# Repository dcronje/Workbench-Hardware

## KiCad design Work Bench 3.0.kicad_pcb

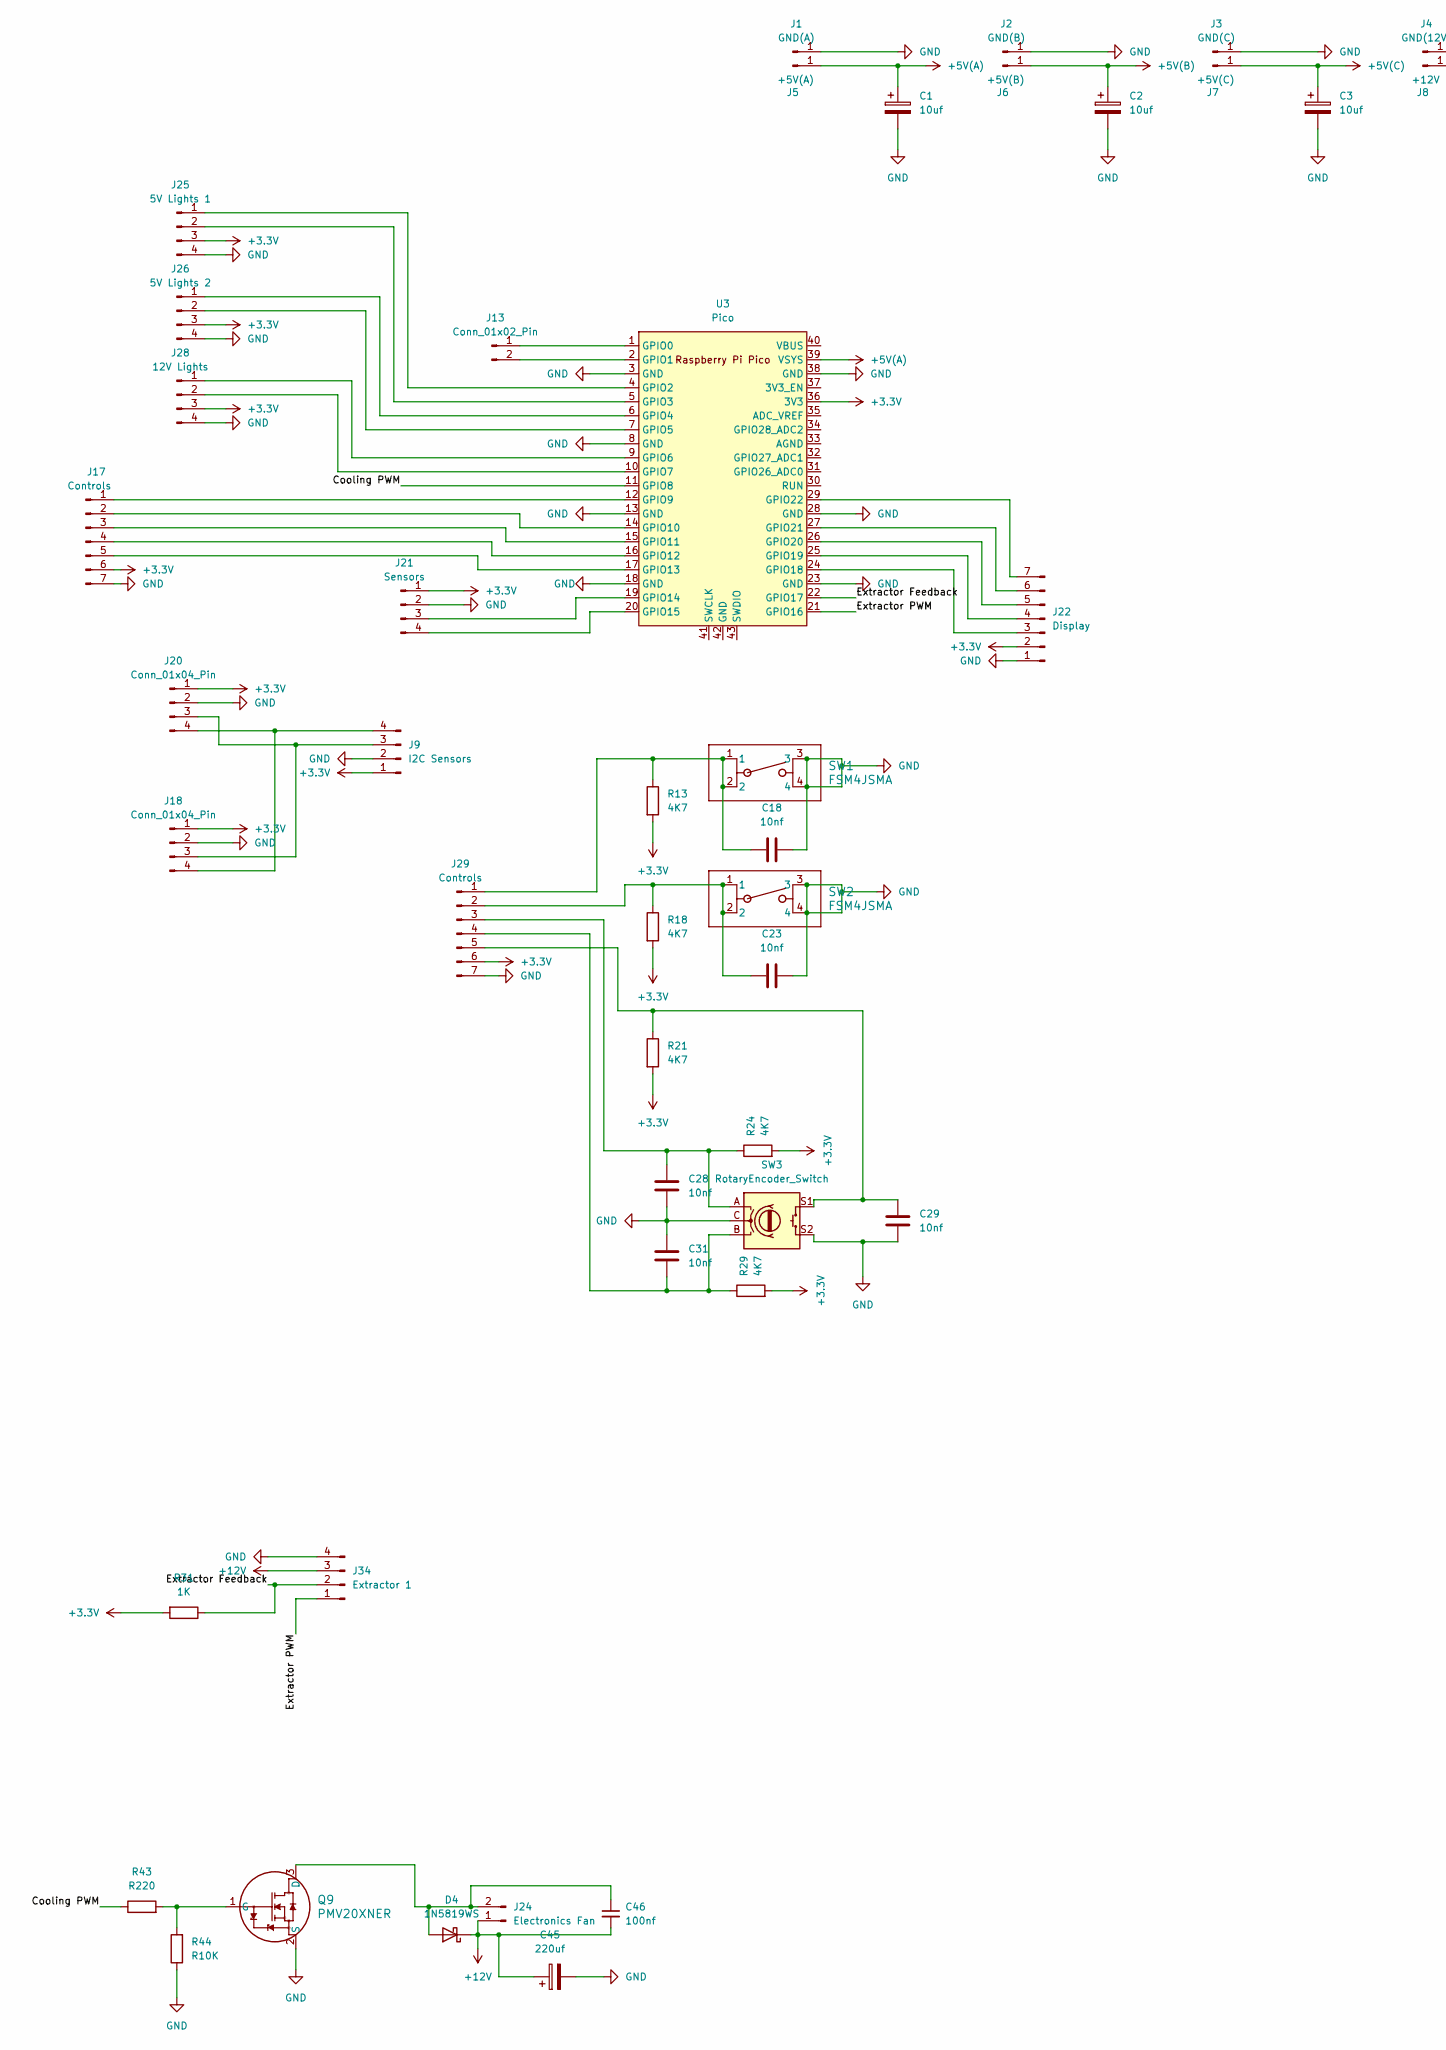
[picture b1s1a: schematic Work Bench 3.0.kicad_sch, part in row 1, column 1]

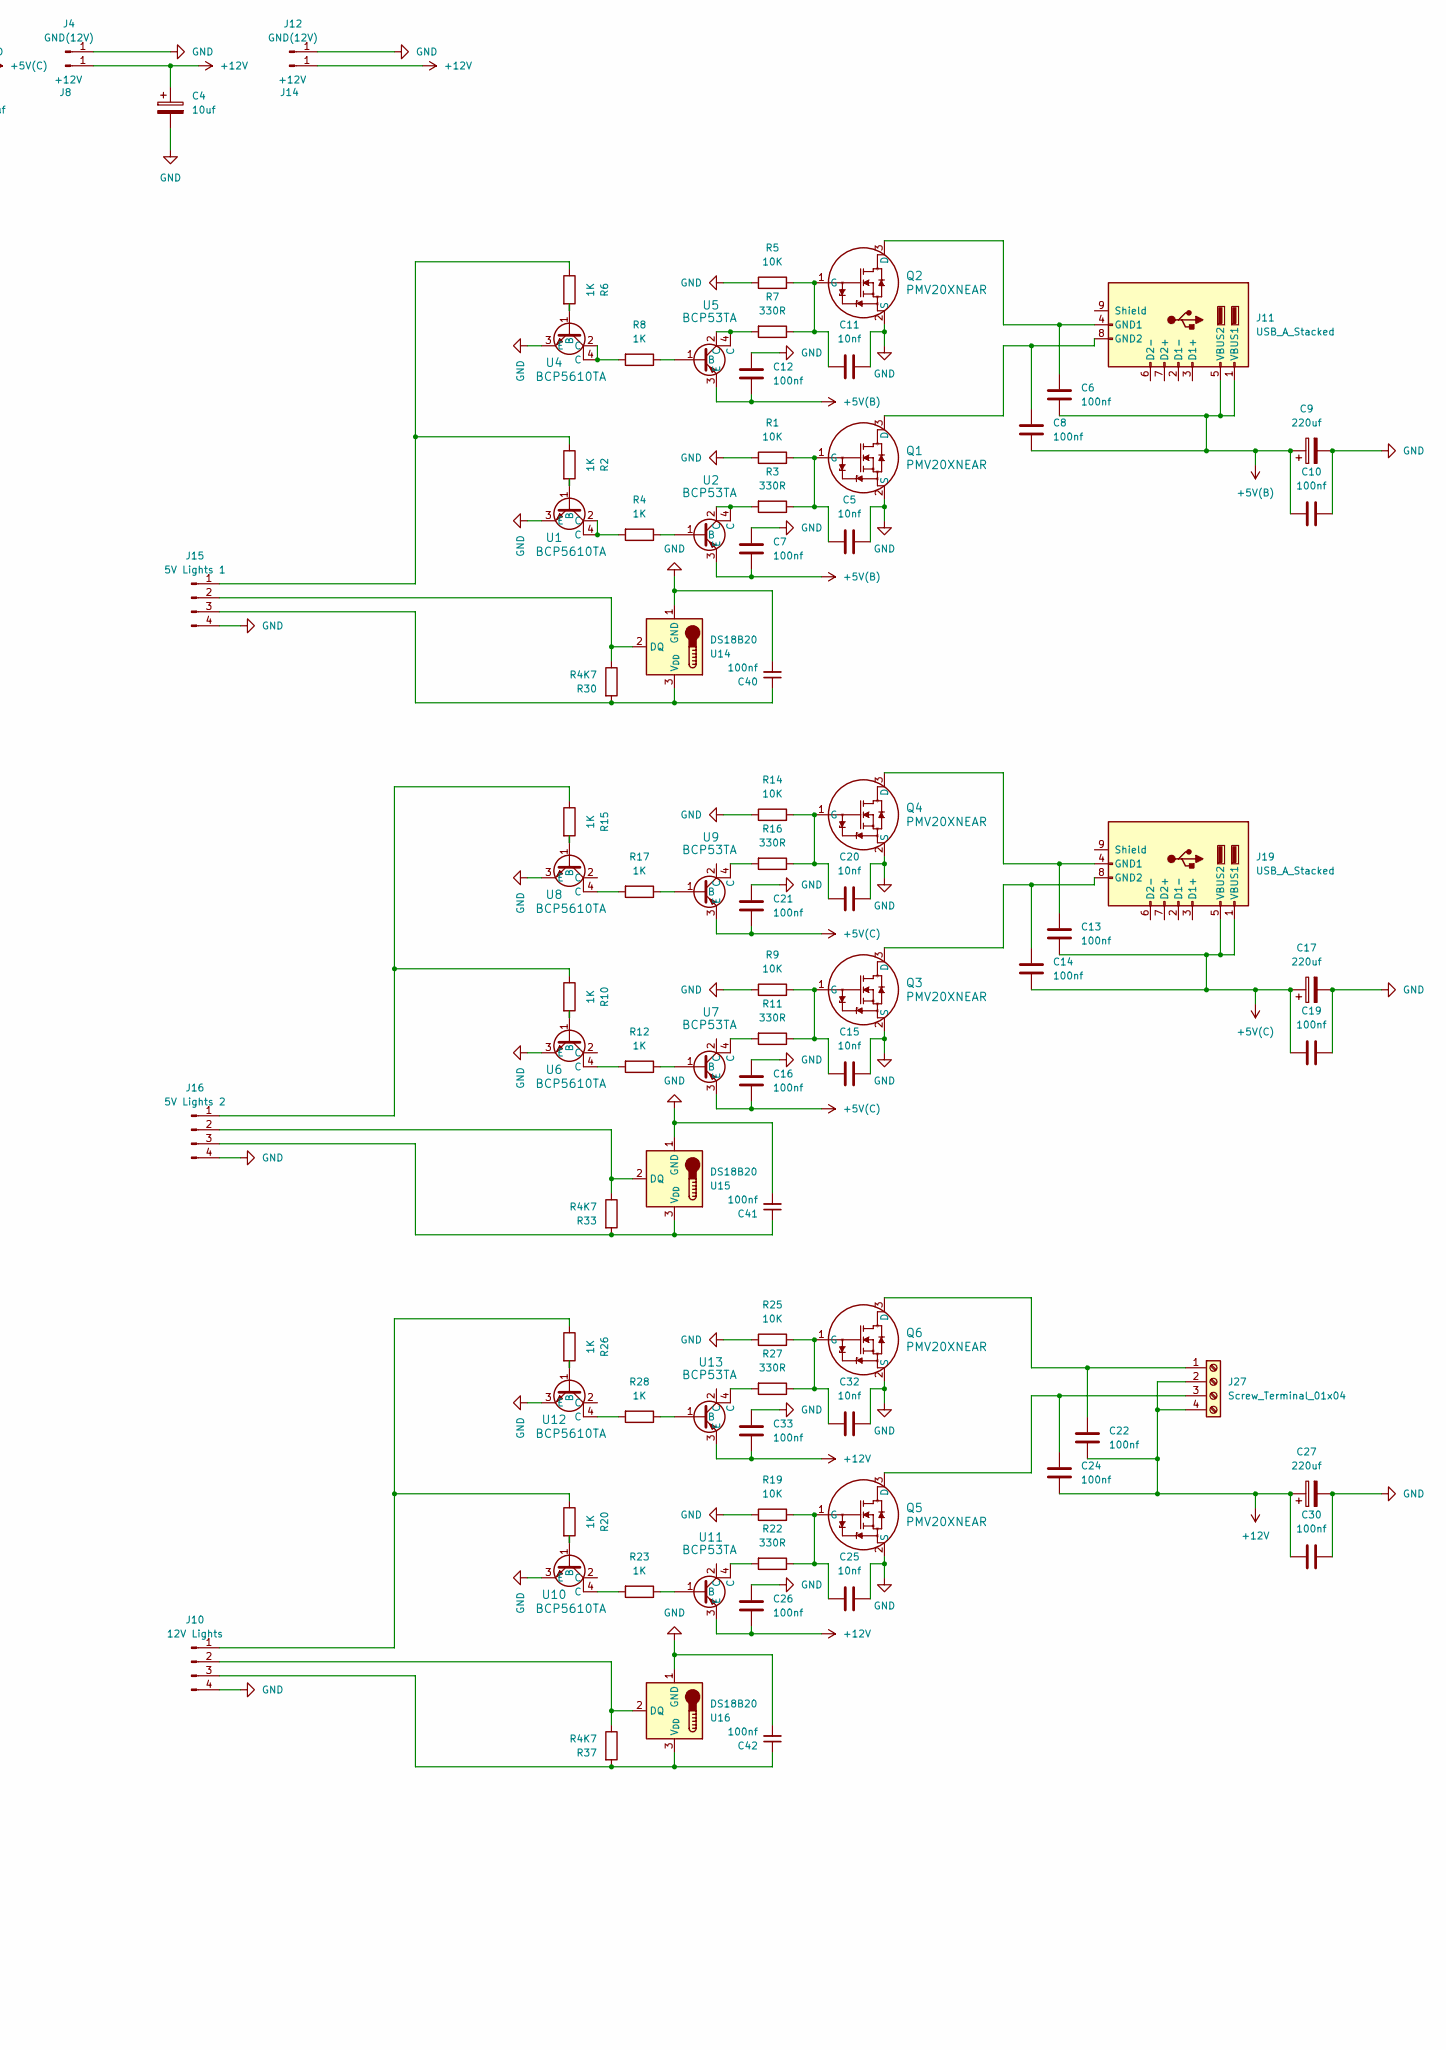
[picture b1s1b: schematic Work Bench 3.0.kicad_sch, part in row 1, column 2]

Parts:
C1, C2, C3, C4: 10uf; CP_Elec_4x5.4
C5, C11, C15, C18, C20, C23, C25, C28, C29, C31, C32: 10nf; C_1206_3216Metric_Pad1.33x1.80mm_HandSolder
C6, C7, C8, C10, C12, C13, C14, C16, C19, C21, C22, C24, C26, C30, C33: 100nf; C_1210_3225Metric_Pad1.33x2.70mm_HandSolder
C9, C17, C27: 220uf; C_Elec_8x10.2
C40, C41, C42, C46: 100nf; C_1210_3225Metric
C45: 220uf; CP_Elec_8x10.5
D4: 1N5819WS; D_SOD-323
J1: GND(A); SolderWirePad_1x01_SMD_5x10mm
J2: GND(B); SolderWirePad_1x01_SMD_5x10mm
J3: GND(C); SolderWirePad_1x01_SMD_5x10mm
J4, J12: GND(12V); SolderWirePad_1x01_SMD_5x10mm
J5: +5V(A); SolderWirePad_1x01_SMD_5x10mm
J6: +5V(B); SolderWirePad_1x01_SMD_5x10mm
J7: +5V(C); SolderWirePad_1x01_SMD_5x10mm
J8, J14: +12V; SolderWirePad_1x01_SMD_5x10mm
J9: I2C Sensors; PinHeader_1x04_P2.54mm_Vertical
J10, J28: 12V Lights; SMD-PinHeader_1x04_P2.54mm_Vertical
J11, J19: USB_A_Stacked; USB_A_CUI_UJ2-ADH-TH_Horizontal_Stacked
J13: Conn_01x02_Pin; SMD-PinHeader_1x02_P2.54mm_Vertical
J15, J25: 5V Lights 1; SMD-PinHeader_1x04_P2.54mm_Vertical
J16, J26: 5V Lights 2; SMD-PinHeader_1x04_P2.54mm_Vertical
J17: Controls; SMD-PinHeader_1x07_P2.54mm_Vertical
J18, J20: Conn_01x04_Pin; SMD-PinHeader_1x04_P2.54mm_Vertical
J21: Sensors; SMD-PinHeader_1x04_P2.54mm_Vertical
J22: Display; SMD-PinHeader_1x07_P2.54mm_Vertical
J24: Electronics Fan; SMD-PinHeader_1x02_P2.54mm_Vertical
J27: Screw_Terminal_01x04; TerminalBlock_bornier-4_P5.08mm
J29: Controls; PinHeader_1x07_P2.54mm_Vertical
J34: Extractor 1; SMD-PinHeader_1x04_P2.54mm_Vertical
Q1, Q2, Q3, Q4, Q5, Q6: PMV20XNEAR; SOT23-TO-236AB_NEX
Q9: PMV20XNER; SOT23-TO-236AB_NEX
R1, R5, R9, R14, R19, R25: 10K; R_1206_3216Metric_Pad1.30x1.75mm_HandSolder
R2, R4, R6, R8, R10, R12, R15, R17, R20, R23, R26, R28, R31: 1K; R_1206_3216Metric_Pad1.30x1.75mm_HandSolder
R3, R7, R11, R16, R22, R27: 330R; R_1206_3216Metric_Pad1.30x1.75mm_HandSolder
R13, R18, R21, R24, R29: 4K7; R_1206_3216Metric_Pad1.30x1.75mm_HandSolder
R30, R33, R37: R4K7; R_1206_3216Metric
R43: R220; R_1206_3216Metric
R44: R10K; R_1206_3216Metric
SW1, SW2: FSM4JSMA; SW4_FSM4JSMA_TEC
SW3: RotaryEncoder_Switch; RotaryEncoder_Alps_EC11E-Switch_Vertical_H20mm
U1, U4, U6, U8, U10, U12: BCP5610TA; SOT-223_DIO
U2, U5, U7, U9, U11, U13: BCP53TA; SOT-223_DIO
U3: Pico; RPi_Pico_SMD_TH
U14, U15, U16: DS18B20; DS18B20_SMD

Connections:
+3.3V: J9.1, J17.6, J18.1, J20.1, J21.1, J22.2, J25.3, J26.3, J28.3, J29.6, R13.2, R18.2, R21.2, R24.2, R29.2, R31.2, U3.36 (3V3)
+5V(A): C1.1, J5.1, U3.39 (VSYS)
+5V(B): C2.1, C6.1, C7.2, C8.1, C9.1, C10.1, C12.2, J6.1, J11.1 (VBUS1), J11.5 (VBUS2), U2.3 (E), U5.3 (E)
+5V(C): C3.1, C13.1, C14.1, C16.2, C17.1, C19.1, C21.2, J7.1, J19.1 (VBUS1), J19.5 (VBUS2), U7.3 (E), U9.3 (E)
+12V: C4.1, C22.1, C24.1, C26.2, C27.1, C30.1, C33.2, C45.1, C46.2, D4.1 (K), J8.1, J14.1, J24.1, J27.2, J27.4, J34.3, U11.3 (E), U13.3 (E)
/Cooling PWM: R43.1, U3.11 (GPIO8)
/Extractor Feedback: J34.2, R31.1, U3.22 (GPIO17)
/Extractor PWM: J34.1, U3.21 (GPIO16)
GND: C1.2, C2.2, C3.2, C4.2, C5.2, C7.1, C9.2, C10.2, C11.2, C12.1, C15.2, C16.1, C17.2, C18.2, C19.2, C20.2, C21.1, C23.2, C25.2, C26.1, C27.2, C28.1, C29.2, C30.2, C31.2, C32.2, C33.1, C40.2, C41.2, C42.2, C45.2, J1.1, J2.1, J3.1, J4.1, J9.2, J10.4, J12.1, J15.4, J16.4, J17.7, J18.2, J20.2, J21.2, J22.1, J25.4, J26.4, J28.4, J29.7, J34.4, Q1.2 (S), Q2.2 (S), Q3.2 (S), Q4.2 (S), Q5.2 (S), Q6.2 (S), Q9.2 (S), R1.1, R5.1, R9.1, R14.1, R19.1, R25.1, R44.1, SW1.3, SW1.4, SW2.3, SW2.4, SW3.C, SW3.S2, U1.3 (E), U3.3 (GND), U3.8 (GND), U3.13 (GND), U3.18 (GND), U3.23 (GND), U3.28 (GND), U3.38 (GND), U4.3 (E), U6.3 (E), U8.3 (E), U10.3 (E), U12.3 (E), U14.1 (GND), U15.1 (GND), U16.1 (GND)
unnamed: C46.1, D4.2 (A), J24.2, Q9.3 (D)
unnamed: J10.1, R20.1, R26.1
unnamed: J10.2, R37.1, U16.2 (DQ)
unnamed: C42.1, J10.3, R37.2, U16.3 (V_{DD})
unnamed: C6.2, J11.4 (GND1), Q2.3 (D)
unnamed: C8.2, J11.8 (GND2), Q1.3 (D)
unnamed: J13.1, U3.1 (GPIO0)
unnamed: J13.2, U3.2 (GPIO1)
unnamed: J15.1, R2.1, R6.1
unnamed: J15.2, R30.1, U14.2 (DQ)
unnamed: C40.1, J15.3, R30.2, U14.3 (V_{DD})
unnamed: J16.1, R10.1, R15.1
unnamed: J16.2, R33.1, U15.2 (DQ)
unnamed: C41.1, J16.3, R33.2, U15.3 (V_{DD})
unnamed: J17.1, U3.12 (GPIO9)
unnamed: J17.2, U3.14 (GPIO10)
unnamed: J17.3, U3.15 (GPIO11)
unnamed: J17.4, U3.16 (GPIO12)
unnamed: J17.5, U3.17 (GPIO13)
unnamed: J9.3, J18.3, J20.3
unnamed: J9.4, J18.4, J20.4
unnamed: C13.2, J19.4 (GND1), Q4.3 (D)
unnamed: C14.2, J19.8 (GND2), Q3.3 (D)
unnamed: J21.3, U3.19 (GPIO14)
unnamed: J21.4, U3.20 (GPIO15)
unnamed: J22.3, U3.24 (GPIO18)
unnamed: J22.4, U3.25 (GPIO19)
unnamed: J22.5, U3.26 (GPIO20)
unnamed: J22.6, U3.27 (GPIO21)
unnamed: J22.7, U3.29 (GPIO22)
unnamed: J25.1, U3.4 (GPIO2)
unnamed: J25.2, U3.5 (GPIO3)
unnamed: J26.1, U3.6 (GPIO4)
unnamed: J26.2, U3.7 (GPIO5)
unnamed: C22.2, J27.1, Q6.3 (D)
unnamed: C24.2, J27.3, Q5.3 (D)
unnamed: J28.1, U3.9 (GPIO6)
unnamed: J28.2, U3.10 (GPIO7)
unnamed: C18.1, J29.1, R13.1, SW1.1, SW1.2
unnamed: C23.1, J29.2, R18.1, SW2.1, SW2.2
unnamed: C28.2, J29.3, R24.1, SW3.A
unnamed: C31.1, J29.4, R29.1, SW3.B
unnamed: C29.1, J29.5, R21.1, SW3.S1
unnamed: C5.1, Q1.1 (G), R1.2, R3.1
unnamed: C11.1, Q2.1 (G), R5.2, R7.1
unnamed: C15.1, Q3.1 (G), R9.2, R11.1
unnamed: C20.1, Q4.1 (G), R14.2, R16.1
unnamed: C25.1, Q5.1 (G), R19.2, R22.1
unnamed: C32.1, Q6.1 (G), R25.2, R27.1
unnamed: Q9.1 (G), R43.2, R44.2
unnamed: R3.2, U2.2 (C), U2.4 (C)
unnamed: R4.2, U1.2 (C), U1.4 (C)
unnamed: R7.2, U5.2 (C), U5.4 (C)
unnamed: R8.2, U4.2 (C), U4.4 (C)
unnamed: R11.2, U7.4 (C)
unnamed: R12.2, U6.4 (C)
unnamed: R16.2, U9.4 (C)
unnamed: R17.2, U8.4 (C)
unnamed: R22.2, U11.4 (C)
unnamed: R23.2, U10.4 (C)
unnamed: R27.2, U13.4 (C)
unnamed: R28.2, U12.4 (C)
unnamed: R2.2, U1.1 (B)
unnamed: R4.1, U2.1 (B)
unnamed: R6.2, U4.1 (B)
unnamed: R8.1, U5.1 (B)
unnamed: R10.2, U6.1 (B)
unnamed: R12.1, U7.1 (B)
unnamed: R15.2, U8.1 (B)
unnamed: R17.1, U9.1 (B)
unnamed: R20.2, U10.1 (B)
unnamed: R23.1, U11.1 (B)
unnamed: R26.2, U12.1 (B)
unnamed: R28.1, U13.1 (B)

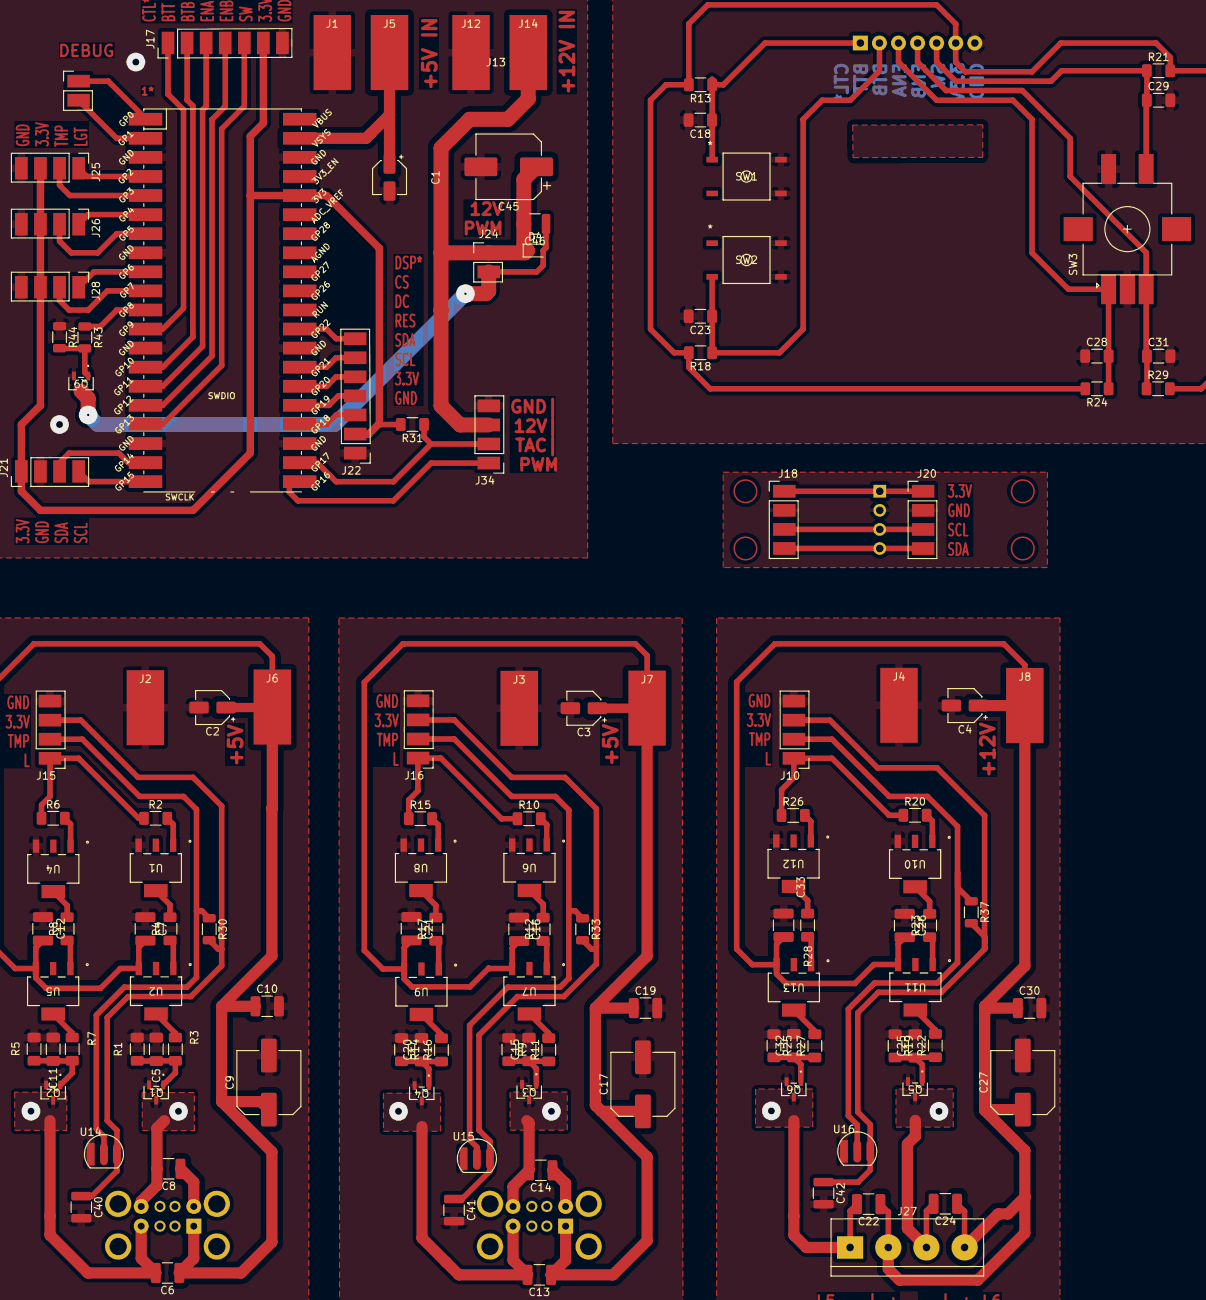
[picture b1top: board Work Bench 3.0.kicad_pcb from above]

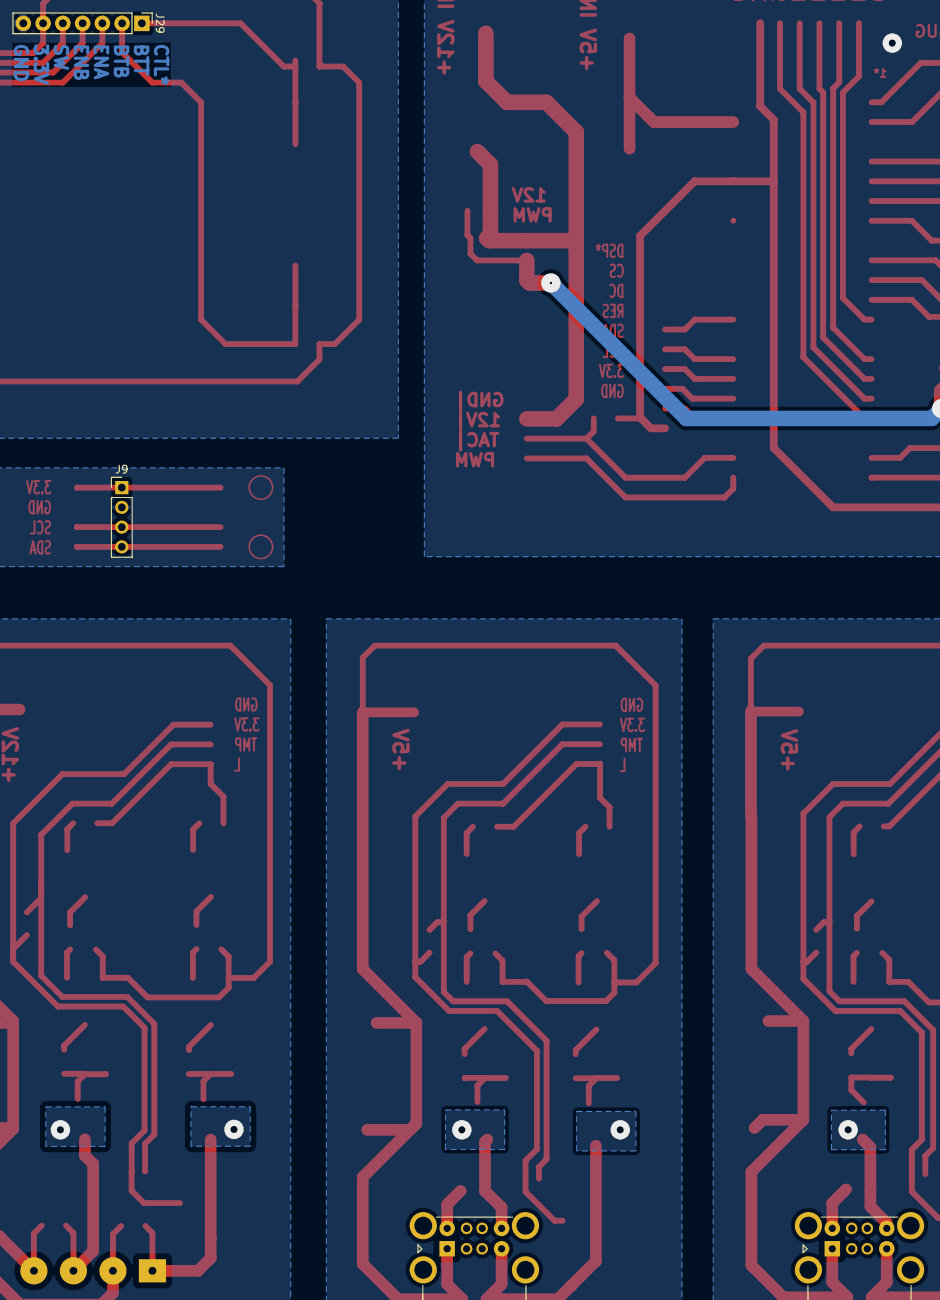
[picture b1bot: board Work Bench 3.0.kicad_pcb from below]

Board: 2 copper layers, 129 parts (4 on the bottom side), 83 nets.

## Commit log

2025-01-08 Done
2025-01-08 Split
